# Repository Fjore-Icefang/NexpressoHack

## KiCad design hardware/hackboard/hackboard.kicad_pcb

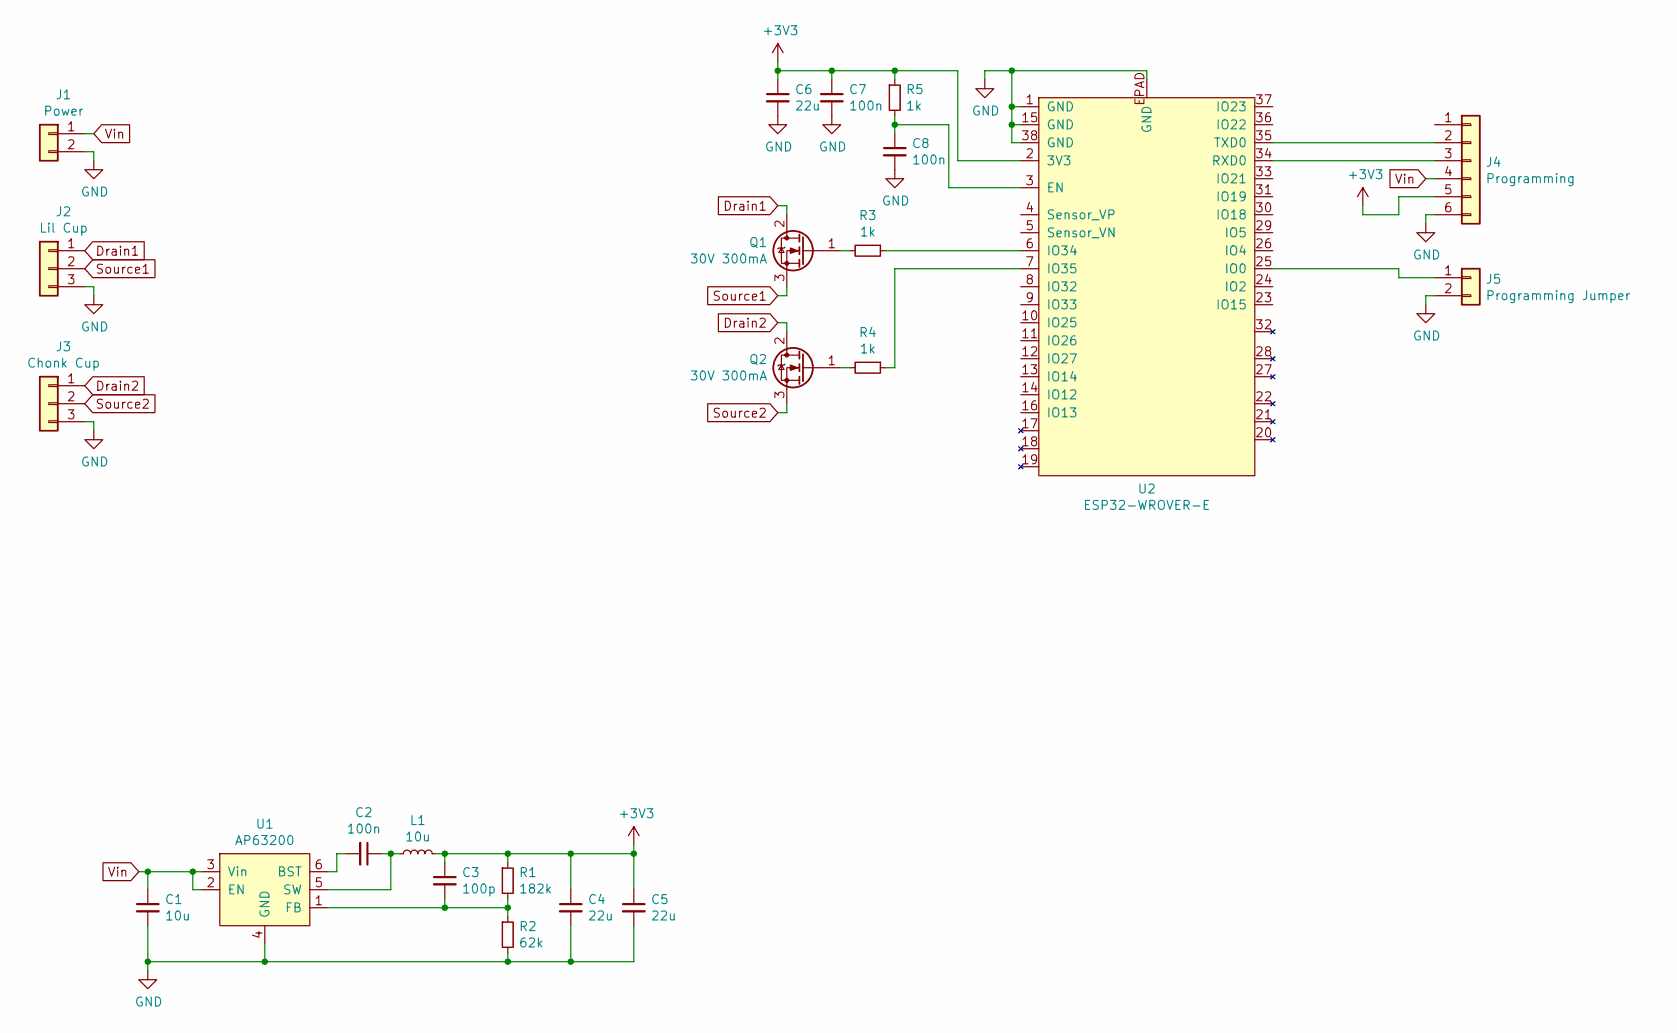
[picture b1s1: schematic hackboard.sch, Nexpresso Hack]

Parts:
C1: 10u; C_1210_3225Metric_Pad1.42x2.65mm_HandSolder
C2, C7, C8: 100n; C_0603_1608Metric_Pad1.05x0.95mm_HandSolder
C3: 100p; C_0402_1005Metric
C4, C5, C6: 22u; C_1210_3225Metric_Pad1.42x2.65mm_HandSolder
J1: Power; Molex_KK-254_AE-6410-02A_1x02_P2.54mm_Vertical
J2: Lil Cup; Molex_KK-254_AE-6410-03A_1x03_P2.54mm_Vertical
J3: Chonk Cup; Molex_KK-254_AE-6410-03A_1x03_P2.54mm_Vertical
J4: Programming; Molex_KK-254_AE-6410-06A_1x06_P2.54mm_Vertical
J5: Programming Jumper; PinHeader_1x02_P2.54mm_Vertical
L1: 10u; WE-7345
Q1, Q2: 30V 300mA; SOT-23_Handsoldering
R1: 182k; R_0603_1608Metric_Pad1.05x0.95mm_HandSolder
R2: 62k; R_0603_1608Metric_Pad1.05x0.95mm_HandSolder
R3, R4, R5: 1k; R_0603_1608Metric_Pad1.05x0.95mm_HandSolder
U1: AP63200; TSOT-23-6_HandSoldering
U2: ESP32-WROVER-E; ESP32-WROOM-ROVER

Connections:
+3V3: C3.1, C4.1, C5.1, C6.1, C7.1, J4.5, L1.2, R1.1, R5.1, U2.2 (3V3)
Drain1: J2.1, Q1.2 (D)
Drain2: J3.1, Q2.2 (D)
GND: C1.2, C4.2, C5.2, C6.2, C7.2, C8.2, J1.2, J2.3, J3.3, J4.6, J5.2, R2.2, U1.4 (GND), U2.1 (GND), U2.15 (GND), U2.38 (GND), U2.EPAD (GND)
unnamed: C2.1, L1.1, U1.5 (SW)
unnamed: C2.2, U1.6 (BST)
unnamed: C3.2, R1.2, R2.1, U1.1 (FB)
unnamed: C8.1, R5.2, U2.3 (EN)
unnamed: J4.2, U2.35 (TXD0)
unnamed: J4.3, U2.34 (RXD0)
unnamed: J5.1, U2.25 (IO0)
unnamed: Q1.1 (G), R3.2
unnamed: Q2.1 (G), R4.2
unnamed: R3.1, U2.6 (IO34)
unnamed: R4.1, U2.7 (IO35)
Source1: J2.2, Q1.3 (S)
Source2: J3.2, Q2.3 (S)
Vin: C1.1, J1.1, J4.4, U1.2 (EN), U1.3 (Vin)

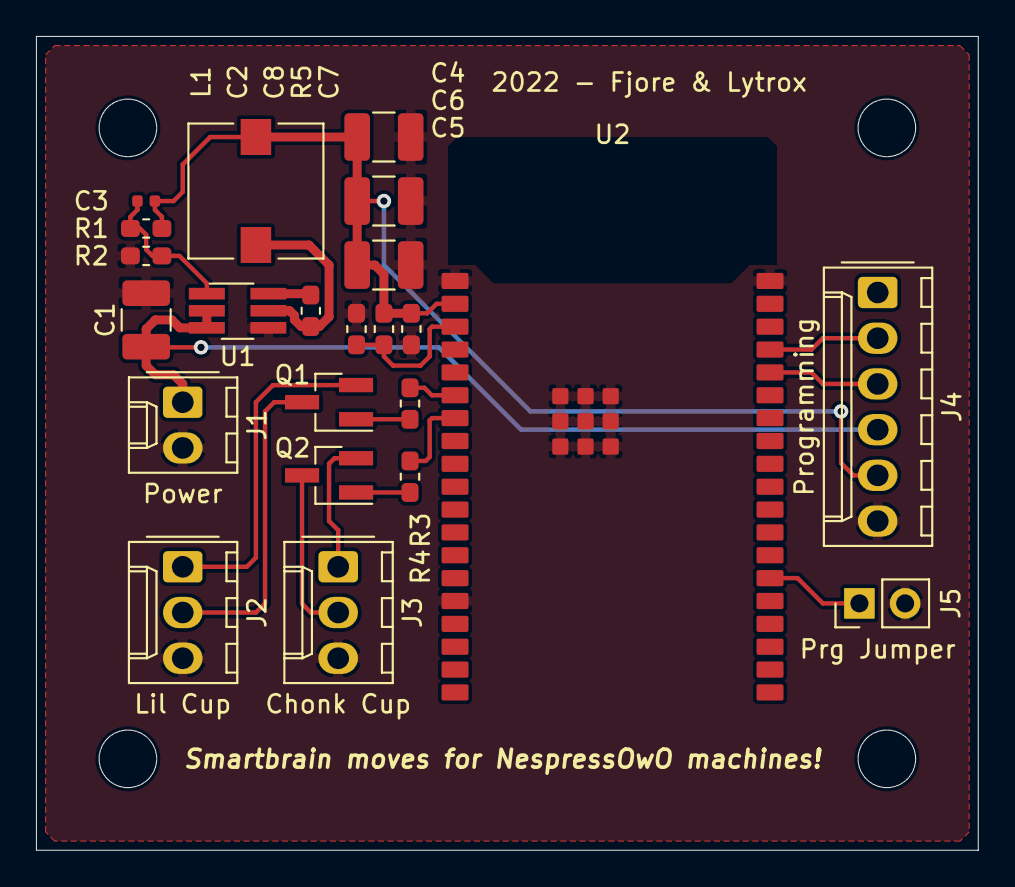
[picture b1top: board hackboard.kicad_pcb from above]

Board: 2 copper layers, 52.3 x 45.2 mm, 23 parts (0 on the bottom side), 18 nets.

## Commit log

2022-03-17 First version electronic schematic
2022-03-24 Footprints zugewiesen, Bauteile angefangen zu plazieren
2022-03-24 PCB fertiggestellt
